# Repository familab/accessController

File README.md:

FamiLAB Access Controller
=========================

Access Control software written for FamiLAB.

## Components

### Access Control Point

- Badge scanner and door unlock trigger.
- Microcontroller written in CircuitPython.
- Reads badge, calls auth server, if ✅ then open door.

See [nfc/README.md](./nfc/README.md)

### Authentication Server

- HTTP server written in Typescript.
- Exposes `/access` endpoint.
- `/access` endpoint fetches badge list from Google Sheets for validation.

See [api/README.md](./api/README.md)

--------------------------------

## Development Setup

1. Install Node 18+
2. Globally install `pnpm`
    ```bash
    npm install --global pnpm
    ```
3. Install Node packages
    ```bash
    pnpm install
    ```
4. Follow Development Setup instructions for the sub-project you wish to work on.

--------------------------------

## Deployment Process

The Docker image is built via GitHub Actions whenever a new commit is merged into the `release/v4` branch. The image is
therefore tagged `ghcr.io/familab/accesscontroller:release-v4`.

The server application is composed of multiple docker containers defined by the `./access-controller.stack.yml` Docker
Stack. To deploy this file to the server, you must have a Docker Context set up locally, and then update the Stack using
the stack file.

### Setup Docker Context

On your local machine, create a new [Docker Context](https://docs.docker.com/engine/context/working-with-contexts/) for
the access controller server.

```bash
docker context create familab.accesscontroller --docker "host=ssh://familab@doorcontroller.familab.local.lan"
docker context use familab.accesscontroller
```

Once you run these commands all `docker *` commands you use will target the remote server.

You can always switch back to targeting your local machine by running:

```bash
docker context use default
```

### Update Stack

Once you have a Docker Context set up for the remote server, run the following command to push the Stack.

```bash
docker stack deploy -c "./access-controller.stack.yml" access-controller
```

Make sure to check the logs of the containers to ensure the deployment worked.

--------------------------------

## Project Status

Currently implementing Phase 0.

### Phase 0

Phase 0 is the absolute minimum functionality that allows badge access to the new facility. It is not meant to be
long-term, it is not meant to be well-designed. Has the minimum number of infrastructure dependencies.

#### Requirements

- Working door lock
- ACP that can read badges and unlock door
- WiFi network without Internet

#### Functionality

1. User scans badge
2. ACP calls Auth Server with badge and location
3. Auth Server checks against hardcoded list and responds ✅/❌
4. If user has access, ACP triggers relay to unlock door

#### Hardware

- ACP: ESP-32 and MFRC522 connected on a breadboard, possibly powered by USB
- Auth Server: Living on a raspberry pi or something

#### Component Diagram

### Phase 1

This is the first _real_ version of the access control system.

#### Requirements

- 12/24v DC power line run to the door location
- Internet access

#### Functionality

1. User scans badge
2. ACP calls Auth Server with badge and location
3. Auth Server fetches Google Sheet contents (or checks cache) and responds ✅/❌
4. If user has access, ACP triggers relay to unlock door

#### Hardware

- ACP: MFRC522 mounted outside door, ESP32 mounted inside. Powered by hardwired DC.
- Auth Server: Can still be on temp hardware, but now has internet access.

#### Component Diagram

### Phase 2

Some enhancements that can be made in the future, fairly independently.

#### Permanent ACP hardware build

- Manufactured PCB
- External antenna for MFRC522
- Status LED/display

#### Central Relay Board

- Centralized relay board that powers all door locks
- ACP would then not be responsible for door lock, just communicating with auth server
- All power control in one place
- Allows for remote opening of doors, doors unlocked for open house, etc.

#### Better Auth Server hosting/networking security

- Permanent hosting infrastructure, more reliable server than Raspberry Pi
- Internal DNS hostname would allow for TLS, reduces sniffing/man-in-the-middle attacks
- Put all access control devices on separate subnet/vlan, improves network security

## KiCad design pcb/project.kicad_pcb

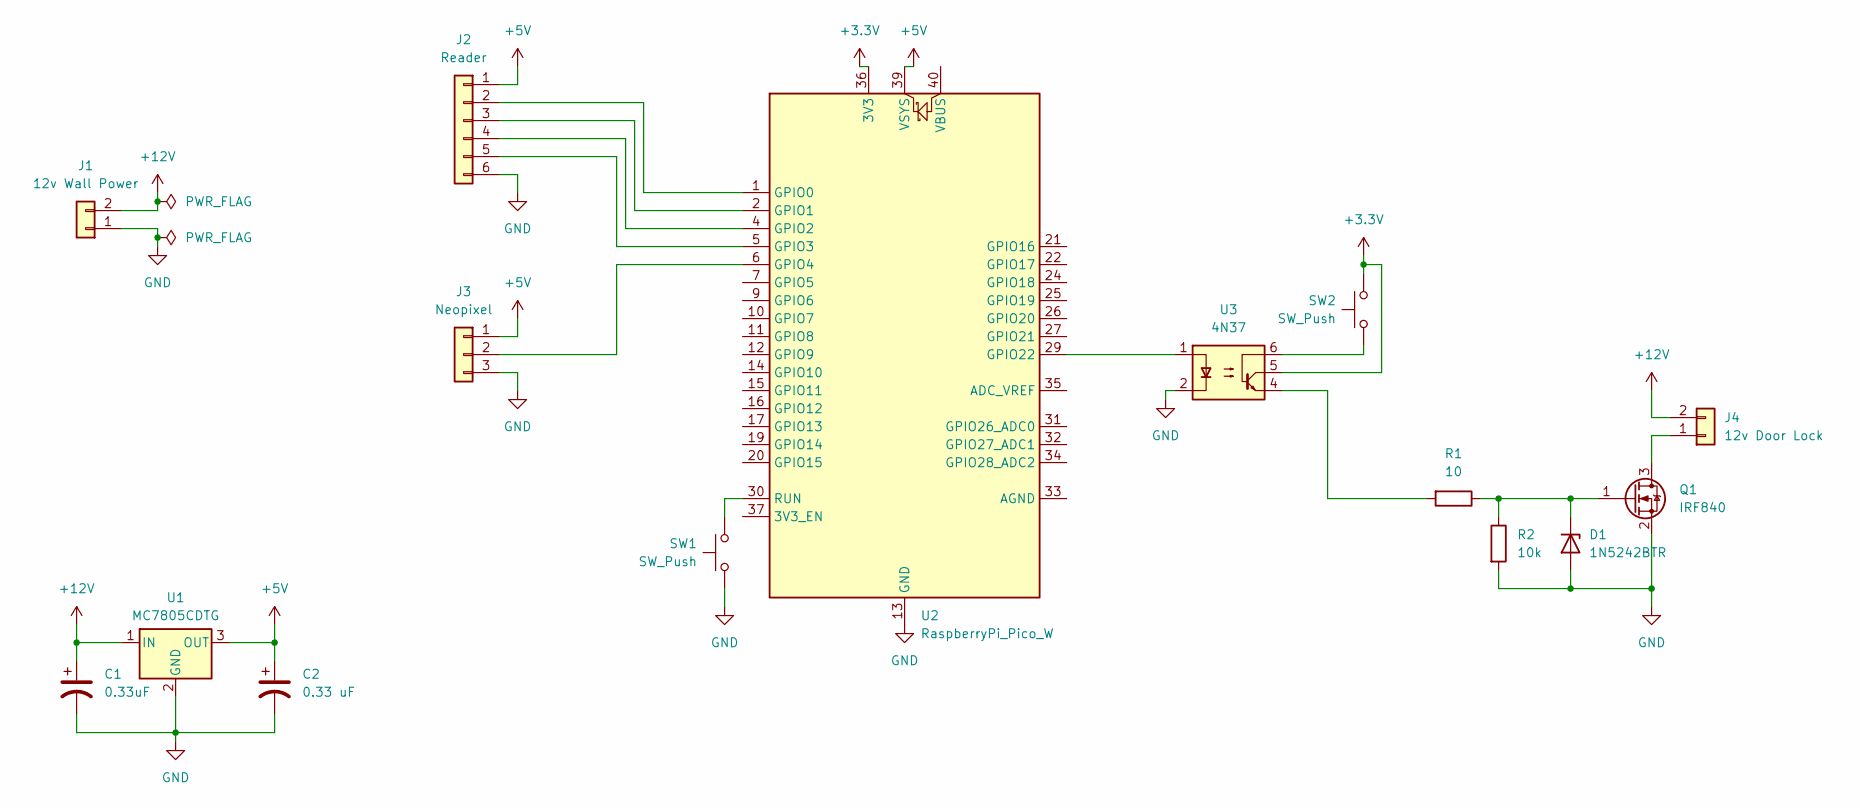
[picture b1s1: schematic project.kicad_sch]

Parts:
C1: 0.33uF; CP_Radial_D5.0mm_P2.00mm
C2: 0.33 uF; CP_Radial_D5.0mm_P2.00mm
D1: 1N5242BTR; D_A-405_P7.62mm_Horizontal
J1: 12v Wall Power; JST_PH_B2B-PH-K_1x02_P2.00mm_Vertical
J2: Reader; JST_PH_B6B-PH-K_1x06_P2.00mm_Vertical
J3: Neopixel; JST_PH_B3B-PH-K_1x03_P2.00mm_Vertical
J4: 12v Door Lock; JST_PH_B2B-PH-K_1x02_P2.00mm_Vertical
Q1: IRF840; TO-220-3_Horizontal_TabDown
R1: 10; R_Axial_DIN0207_L6.3mm_D2.5mm_P10.16mm_Horizontal
R2: 10k; R_Axial_DIN0207_L6.3mm_D2.5mm_P10.16mm_Horizontal
SW1, SW2: SW_Push; SW_PUSH_6mm
U1: MC7805CDTG; TO-252-2
U2: RaspberryPi_Pico_W; RaspberryPi_Pico_Common
U3: 4N37; DIP-6_W7.62mm

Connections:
+3.3V: SW2.1, U2.36 (3V3), U3.5
+5V: C2.1, J2.1, J3.1, U1.3 (OUT), U2.39 (VSYS)
+12V: C1.1, J1.2, J4.2, U1.1 (IN)
GND: C1.2, C2.2, D1.2 (A), J1.1, J2.6, J3.3, Q1.2 (S), R2.2, SW1.2, U1.2 (GND), U2.3 (GND), U2.8 (GND), U2.13 (GND), U2.18 (GND), U2.23 (GND), U2.28 (GND), U2.38 (GND), U3.2
unnamed: D1.1 (K), Q1.1 (G), R1.1, R2.1
unnamed: J2.2, U2.1 (GPIO0)
unnamed: J2.3, U2.2 (GPIO1)
unnamed: J2.4, U2.4 (GPIO2)
unnamed: J2.5, U2.5 (GPIO3)
unnamed: J3.2, U2.6 (GPIO4)
unnamed: J4.1, Q1.3 (D)
unnamed: R1.2, U3.4
unnamed: SW2.2, U3.6
unnamed: U2.29 (GPIO22), U3.1
unnamed: SW1.1, U2.30 (RUN)

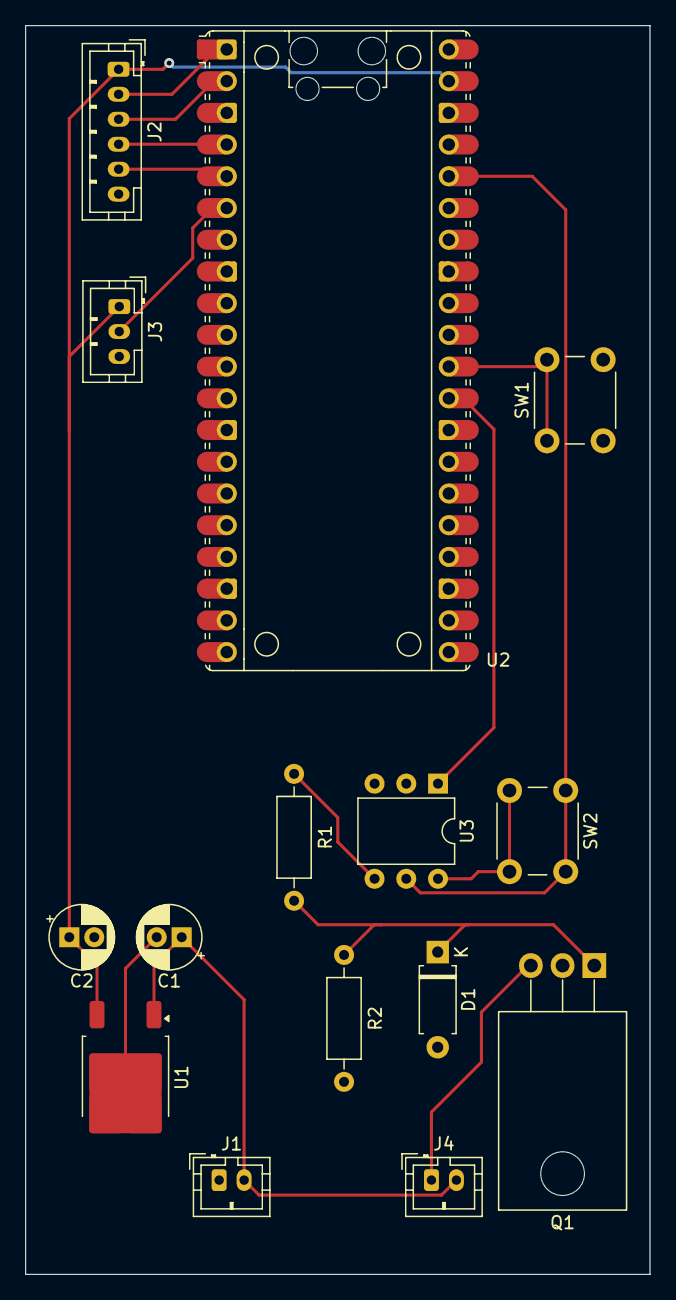
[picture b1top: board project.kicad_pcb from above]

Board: 2 copper layers, 50.0 x 100.0 mm, 15 parts (0 on the bottom side), 15 nets.

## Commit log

2014-12-20 UDP broadcasts and reponses are complete (NEED PACKET DEFFINITION) Started DB, Need to change to an ORM Started Serial, Needs testing and tst harness Needs proper unit tests Needs REST Service Needs 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
2014-12-26 Adds EditorConfig
2015-03-06 Switch to a python library and basic project layout
2015-03-06 add test setup and travis
2015-03-06 fix python3 test
2015-03-06 Added Gitter badge
2015-07-01 remove try 1
2015-07-01 Create api folder for backend
2015-07-01 add requirements and links to libs
2015-07-01 Downgrade es6-module-loader, pull in wrapper code
2015-07-01 add schema, and setup for sqlite3
2015-07-01 update schema, add migrations
2015-07-01 moves to code that can run on node 10
2015-07-01 Base angular app
2015-07-01 Adds timestamp
2015-07-01 Adds api boiler plate
2015-07-01 add test data
2015-07-01 Adds Members page, Removes excess boilerplate
2015-07-01 Adds Body parser
2015-07-01 adds get functions
2015-07-01 add delete
2015-07-01 Adds new members modal
2015-07-01 Adds active state checker via ui-sref-active
2015-07-01 Return 201 on create
2015-07-05 Change api/api to api/routes
2015-07-05 Adds swap files to ignore
2015-07-05 Adds state and route for adding members
2015-07-08 Adds sql for adding and updating members
2015-07-08 switch to serial instead of libnfc
2015-07-08 add ardunio code and remove writeln section of test serial code
2015-07-08 fix config values
2015-07-08 add door open/close and stub code for serial, db check and door
2015-07-08 fix path to config
2015-07-08 log error
2015-07-08 fix typo in cards.js
2015-07-08 add sql query
2015-07-08 you have to select something
2015-07-08 Finshes Member Creation and Update flow
    * Adds ability to update member information
    * Adds ability to delete members
    * Adds ability to add cards
    * Adds ability to delete cards
    * Adds ability to update cards
    * Adds name field to cards table
2015-07-08 remove quotes around params
2015-07-08 Allow to work in DEV or PROD
    * If using Rpi, add PROD=true environment to enable Serial and GPIO
    * PROD=TRUE nodemon server.js
2015-07-08 test the response from the db
2015-07-08 add missing '}'
2015-07-08 fix grouping
2015-07-08 add message if a user is denied access
2015-07-08 strip carraige return and linefeed from string
2015-07-08 change var name from data to uid
2015-07-08 declare uid
2015-07-08 replace /r /n correctly
2015-07-08 add the correct uid to the db and some cleanup in server.js
2015-07-08 Adds enable/disable feature and event for repolling members
2015-07-08 add loggin
2015-07-08 change to UTCstring
2015-07-08 Adds access log directive
2015-07-08 update logs sqln
2015-07-08 Adds UI for logs
2015-07-08 Clean up access log ui. Filter date
2015-07-08 Move logs above hr
2015-07-08 Updates insert of cards to add name
2015-07-27 Laser Cut Parts
    Added parts to laser cut to fit front of single gang box. Parts will
    need revision.
2015-07-29 update ardunio code, sort logs newest
2015-07-29 fix order by
2015-07-29 move limit to end
2015-07-29 update config, add parser for serial
2015-07-29 fix parameter order
2015-09-28 switch to es6, sequelize and swagger
2015-09-28 stubbed some udp and logic
2017-02-21 Initial Commit. Added readme with implementation plan.
2017-03-04 Setup two way communication
2017-03-05 Add reboot support, and send heartbeat on boot
2017-03-05 Upload logic and clean up dashboard
2017-03-05 Add support for updating status on boot
2017-03-05 Add Relay Controller and update flows
2017-03-05 Add Fritzing diagrams
2022-07-17 Created new potential backend
    Created a very simple backend that ties into google sheets for data
    management so we don't have to worry about a hardware crash.
    Probably needs some error checking before being ready for deployment
    anywhere. Will also need to check if google charges for using the api
    and how much it is.
2022-07-17 Cleaned up some commented out lines
    Cleaned out debug and commented out lines
2022-07-17 Updating template
    Updated template file with additional fields and nots on formatting.
2022-07-17 Cleaned up repository
    Removed submodules that will no longer be necessary for the v2 rewrite.
2022-08-28 Updated readme files
    Updated readme files with more details for current project status and
    design decisions.
2022-10-06 Added logging
    Added winston logging. Logs access requests to console and to disk. May
    need to add log rotation at some point.
2022-10-18 Fixed logic on checkAccess
    Fixed logic to properly return TRUE/FALSE when access is/is not granted.
    Updated readme with plans for how to handle caching.
2023-01-11 nfc_v2 initial commit
    Added proof of concept for connecting to wifi and fetching from URL and
    drawing to screen. This is only tested on the Adafruit ESP32-S3 TFT
    Feather so far
2023-02-18 nfc_v2: added basic NFC reading
    Added code to interact with nfc reader. Currently functional for
    mifare1k tags, need to edit to support the kind of cards we use for
    badges.
2024-02-17 Component setup
2024-02-20 Rework
2024-02-20 Implemented sync script for board devlopment
2024-02-20 Fixed the shared SPI issue
2024-02-20 Improved coloring
2024-02-20 Implemented Wifi
2024-02-20 Use enums for MFRC522 registers/commands
2024-02-20 Pi Pico support
2024-02-20 Properly read FamiLAB badges
2024-02-20 Prev Work
2024-02-20 Cleanup
2024-02-20 Base Implementation
2024-02-21 Created system diagram
2024-02-21 Remove login (need to revisit auth)
2024-02-21 Temp
2024-02-21 Added entity graph diagram and `POST /api/access` flowchart diagram
2024-02-21 Created `solution.md`
2024-02-21 Styling
2024-02-21 Added some endpoints
2024-02-21 Added `deployment.md`
2024-02-21 Some initial Swagger work
2024-02-21 Added Swagger API Explorer for Auth Server
2024-02-21 Clean
2024-02-21 Updated README: - Added component descriptions - Added phase list - Added component diagram per phase
2024-02-24 Added relay pin
2024-02-25 Updated credentials env vars
2024-02-25 Rotated screen
2024-02-25 Created dockerfile and publish workflow
2024-03-10 API timestamp cache
2024-03-14 Improved Board Configuration
2024-03-14 Logger
2024-03-14 Neopixel
2024-03-14 Swapped MFRC522 for PN532
2024-03-14 Added local media cache, improved env vars
2024-03-14 Slight documentation
2024-03-15 Some work
2024-03-21 Rename files
2024-03-21 Logger fix
2024-03-21 Added database models
2024-03-21 Created KiCad project
2024-04-19 Updated service env var handling to allow for pulling secrets from the filesystem
2024-04-19 Enabled Docker multiplatform build so image will work on Raspberry Pi
2024-04-19 Added deployment instructions
2024-04-19 Added Docker Stack compose file
2024-04-28 Implemented circuit
2024-04-28 Added Pi Pico libs
2024-04-29 Updated PCB
2024-04-29 Update schematic with feedback
2024-05-23 Deployment troubleshooting
2024-05-30 Current state
2024-06-30 MQTT Upgrade
